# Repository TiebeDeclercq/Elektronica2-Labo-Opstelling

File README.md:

# Elektronica2-Labo-Opstelling

Complete printplaat met alle schakelingen van zowel gelijkrichting als opamps @Vives kortrijk
Met een printbare voet voor betere stabiliteit en geen kortsluiting te krijgen.
Op deze voet wordt er gewerkt met heated inserts (M3) voor het monteren van de print.

Het schema is als volgt:

Voor het solderen kan je gebruikmaken van de meegeleverde BOM file, alle componenten zijn 0805 buiten sommige TH componenten (omdat deze eigen keuze zijn en makkelijk te verangen moeten zijn)

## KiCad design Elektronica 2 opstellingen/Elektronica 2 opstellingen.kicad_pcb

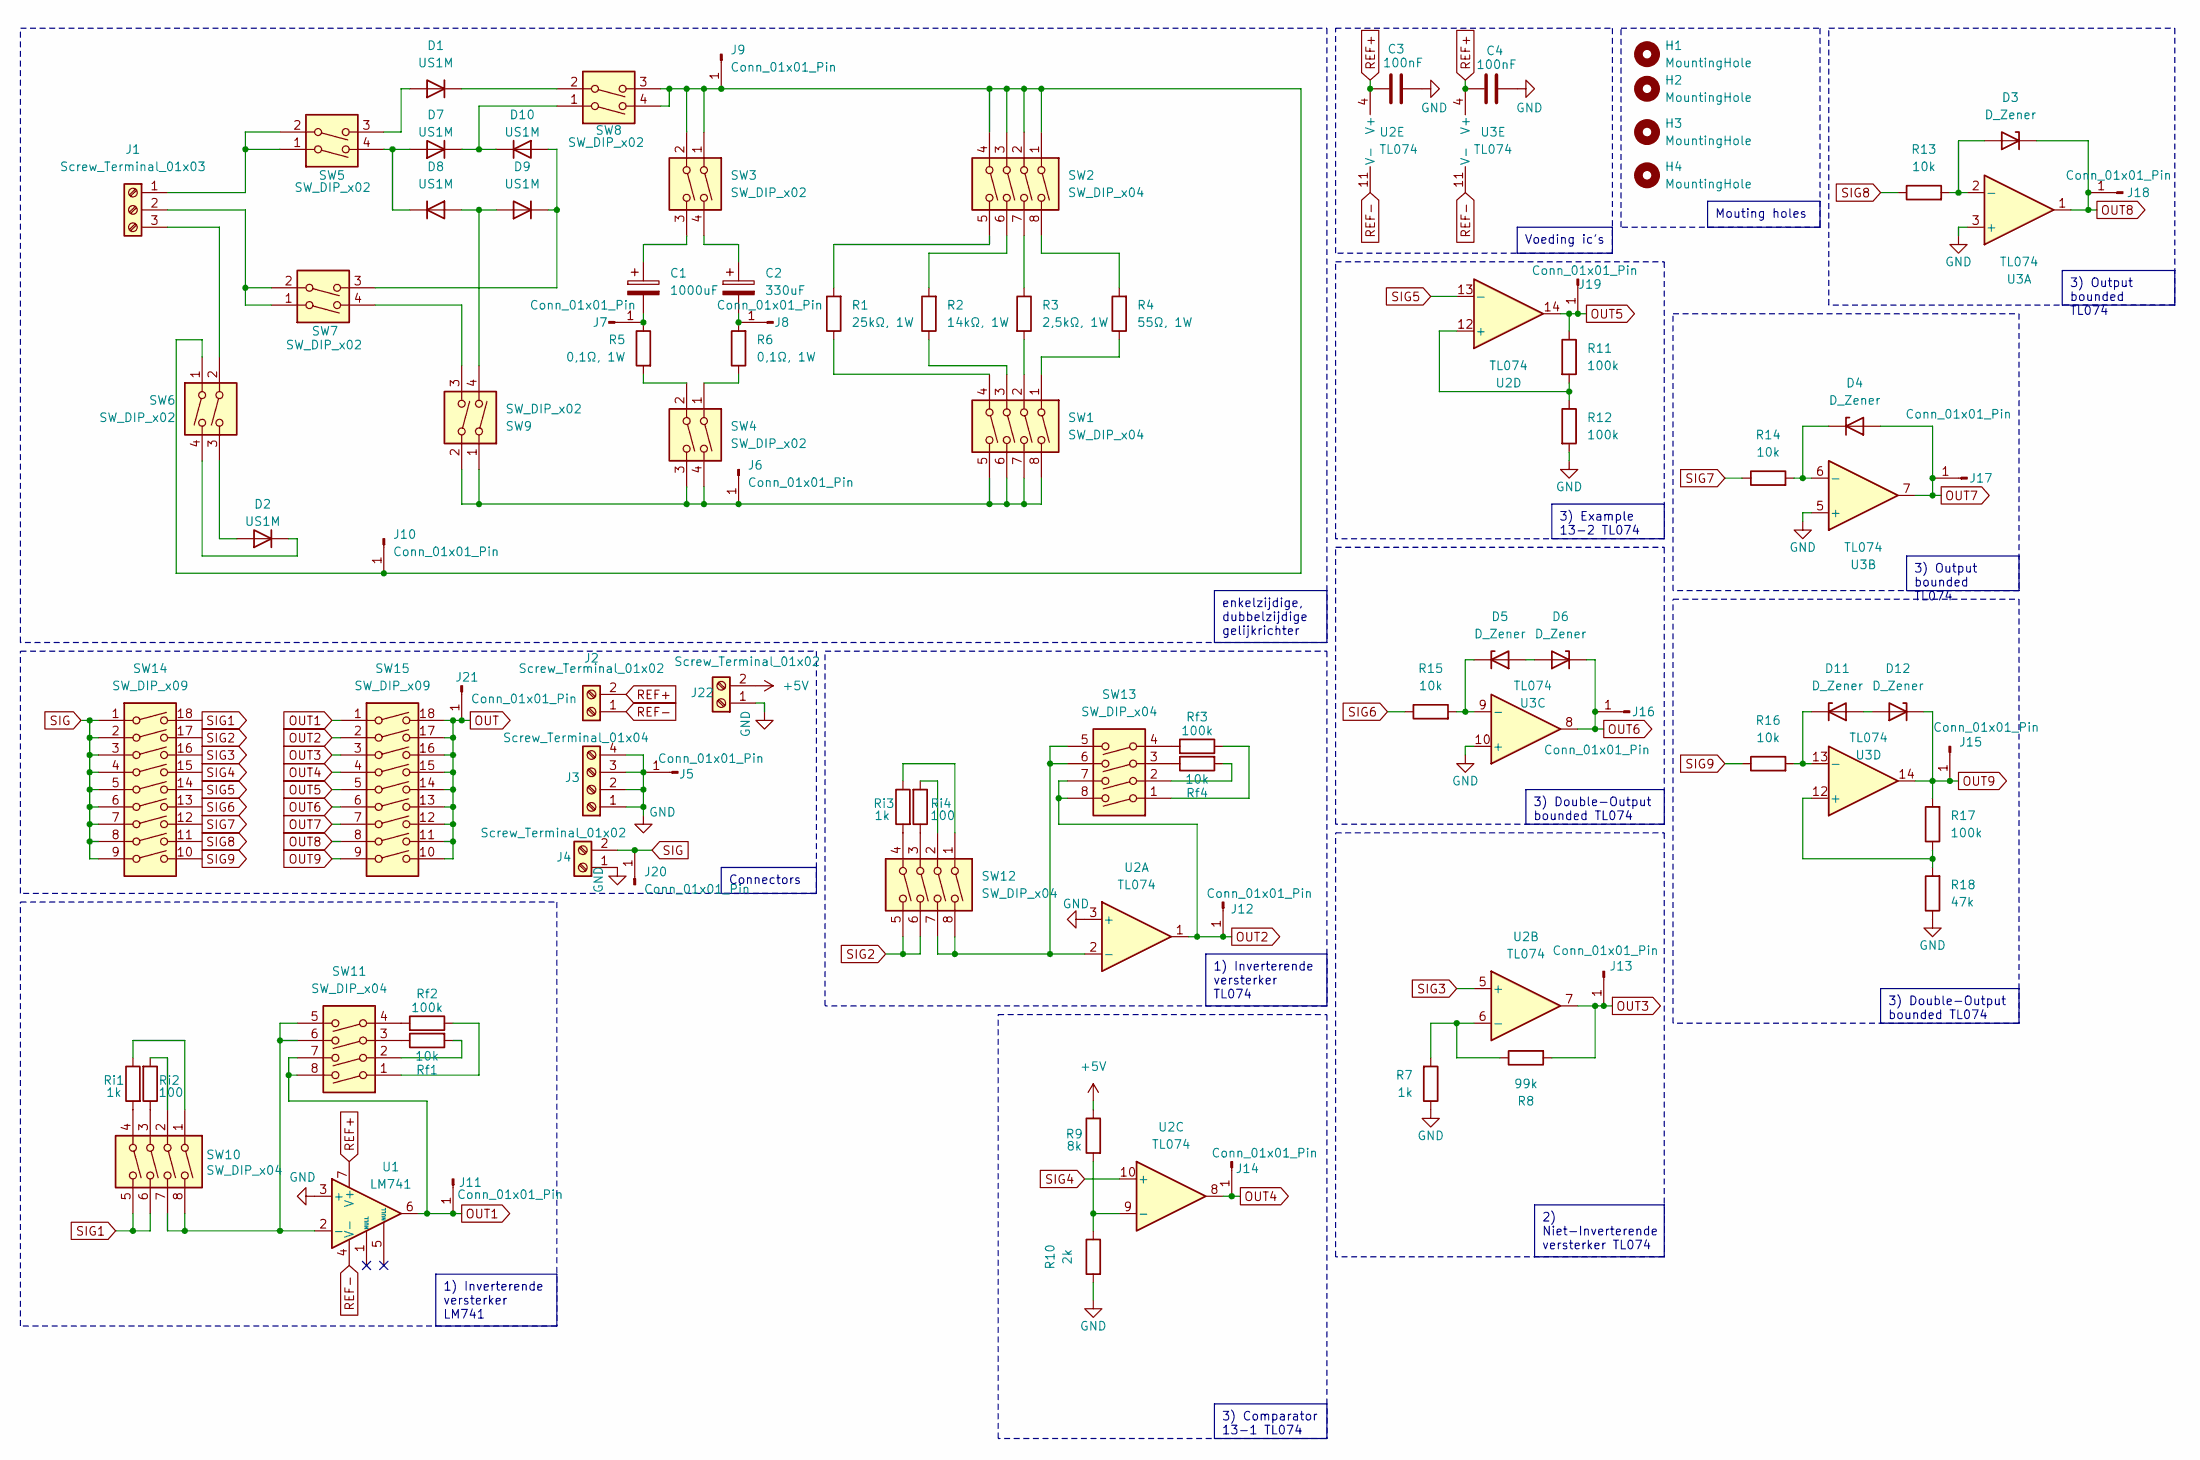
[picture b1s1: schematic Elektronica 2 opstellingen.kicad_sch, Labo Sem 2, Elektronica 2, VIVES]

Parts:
C1: 1000uF; CP_Elec_10x10.5
C2: 330uF; CP_Elec_8x10
C3, C4: 100nF; C_0805_2012Metric
D1, D2, D7, D8, D9, D10: US1M; D_SMA
D3, D4, D5, D6, D11, D12: D_Zener; D_SOD-123
H1, H2, H3, H4: MountingHole; MountingHole_3.2mm_M3
J1: Screw_Terminal_01x03; TerminalBlock_Phoenix_MKDS-1,5-3_1x03_P5.00mm_Horizontal
J2, J4, J22: Screw_Terminal_01x02; TerminalBlock_Phoenix_MKDS-1,5-2_1x02_P5.00mm_Horizontal
J3: Screw_Terminal_01x04; TerminalBlock_Phoenix_MKDS-1,5-4-5.08_1x04_P5.08mm_Horizont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
J5, J6, J7, J8, J9, J10, J11, J12, J13, J14, J15, J16, J17, J18, J19, J20, J21: Conn_01x01_Pin; PinHeader_1x01_P2.54mm_Vertical
R1: 25kΩ, 1W; R_2512_6332Metric
R2: 14kΩ, 1W; R_2512_6332Metric
R3: 2,5kΩ, 1W; R_2512_6332Metric
R4: 55Ω, 1W; R_2512_6332Metric
R5, R6: 0,1Ω, 1W; R_2512_6332Metric
R7: 1k; R_0805_2012Metric
R8: 99k; R_0805_2012Metric
R9: 8k; R_Axial_DIN0207_L6.3mm_D2.5mm_P10.16mm_Horizontal
R10: 2k; R_Axial_DIN0207_L6.3mm_D2.5mm_P10.16mm_Horizontal
R11, R12, R17: 100k; R_Axial_DIN0207_L6.3mm_D2.5mm_P10.16mm_Horizontal
R13, R14, R15, R16: 10k; R_Axial_DIN0207_L6.3mm_D2.5mm_P10.16mm_Horizontal
R18: 47k; R_Axial_DIN0207_L6.3mm_D2.5mm_P10.16mm_Horizontal
Rf1, Rf4: 10k; R_0805_2012Metric
Rf2, Rf3: 100k; R_0805_2012Metric
Ri1, Ri3: 1k; R_0805_2012Metric
Ri2, Ri4: 100; R_0805_2012Metric
SW1, SW2, SW10, SW11, SW12, SW13: SW_DIP_x04; SW_DIP_SPSTx04_Slide_9.78x12.34mm_W7.62mm_P2.54mm
SW3, SW4, SW5, SW6, SW7, SW8, SW9: SW_DIP_x02; SW_DIP_SPSTx02_Slide_9.78x7.26mm_W7.62mm_P2.54mm
SW14, SW15: SW_DIP_x09; SW_DIP_SPSTx09_Slide_9.78x25.04mm_W7.62mm_P2.54mm
U1: LM741; SOIC-8_3.9x4.9mm_P1.27mm
U2, U3: TL074; SOIC-14_3.9x8.7mm_P1.27mm

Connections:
+5V: J22.2, R9.1
GND: C3.2, C4.2, J3.1, J3.2, J3.3, J3.4, J4.1, J5.1, J22.1, R7.1, R10.2, R12.2, R18.1, U1.3 (+), U2.3 (+), U3.3 (+), U3.5 (+), U3.10 (+)
unnamed: C1.1, SW3.3
unnamed: C2.1, SW3.4
unnamed: D1.2 (A), SW5.3
unnamed: D1.1 (K), SW8.2
unnamed: D2.2 (A), SW6.3
unnamed: D2.1 (K), SW6.4
unnamed: D3.2 (A), R13.2, U3.2 (-)
unnamed: D4.1 (K), R14.2, U3.6 (-)
unnamed: D5.2 (A), D6.2 (A)
unnamed: D5.1 (K), R15.2, U3.9 (-)
unnamed: D7.2 (A), D8.1 (K), SW5.4
unnamed: D8.2 (A), D9.2 (A), SW9.4
unnamed: D9.1 (K), D10.2 (A), SW7.3
unnamed: D7.1 (K), D10.1 (K), SW8.1
unnamed: D11.2 (A), D12.2 (A)
unnamed: D11.1 (K), R16.2, U3.13 (-)
unnamed: J1.1, SW5.1, SW5.2
unnamed: J1.2, SW7.1, SW7.2
unnamed: J1.3, SW6.2
unnamed: J6.1, SW1.5, SW1.6, SW1.7, SW1.8, SW4.3, SW4.4, SW9.1, SW9.2
unnamed: C1.2, J7.1, R5.1
unnamed: C2.2, J8.1, R6.2
unnamed: J9.1, J10.1, SW2.1, SW2.2, SW2.3, SW2.4, SW3.1, SW3.2, SW6.1, SW8.3, SW8.4
unnamed: R1.1, SW1.4
unnamed: R1.2, SW2.5
unnamed: R2.1, SW1.3
unnamed: R2.2, SW2.6
unnamed: R3.1, SW2.7
unnamed: R3.2, SW1.2
unnamed: R4.1, SW1.1
unnamed: R4.2, SW2.8
unnamed: R5.2, SW4.2
unnamed: R6.1, SW4.1
unnamed: Rf1.1, SW11.3
unnamed: Rf1.2, SW11.2
unnamed: Rf2.1, SW11.1
unnamed: Rf2.2, SW11.4
unnamed: Rf3.1, SW13.1
unnamed: Rf3.2, SW13.4
unnamed: Rf4.1, SW13.3
unnamed: Rf4.2, SW13.2
unnamed: Ri1.1, SW10.1
unnamed: Ri1.2, SW10.4
unnamed: Ri2.1, SW10.3
unnamed: Ri2.2, SW10.2
unnamed: Ri3.1, SW12.1
unnamed: Ri3.2, SW12.4
unnamed: Ri4.1, SW12.3
unnamed: Ri4.2, SW12.2
unnamed: SW7.4, SW9.3
unnamed: SW10.7, SW10.8, SW11.5, SW11.6, U1.2 (-)
unnamed: SW12.7, SW12.8, SW13.5, SW13.6, U2.2 (-)
unnamed: R7.2, R8.1, U2.6 (-)
unnamed: R9.2, R10.1, U2.9 (-)
unnamed: R11.2, R12.1, U2.12 (+)
unnamed: R17.1, R18.2, U3.12 (+)
OUT: J21.1, SW15.10, SW15.11, SW15.12, SW15.13, SW15.14, SW15.15, SW15.16, SW15.17, SW15.18
OUT1: J11.1, SW11.7, SW11.8, SW15.1, U1.6
OUT2: J12.1, SW13.7, SW13.8, SW15.2, U2.1
OUT3: J13.1, R8.2, SW15.3, U2.7
OUT4: J14.1, SW15.4, U2.8
OUT5: J19.1, R11.1, SW15.5, U2.14
OUT6: D6.1 (K), J16.1, SW15.6, U3.8
OUT7: D4.2 (A), J17.1, SW15.7, U3.7
OUT8: D3.1 (K), J18.1, SW15.8, U3.1
OUT9: D12.1 (K), J15.1, R17.2, SW15.9, U3.14
REF+: C3.1, C4.1, J2.2, U1.7 (V+), U2.4 (V+), U3.4 (V+)
REF-: J2.1, U1.4 (V-), U2.11 (V-), U3.11 (V-)
SIG: J4.2, J20.1, SW14.1, SW14.2, SW14.3, SW14.4, SW14.5, SW14.6, SW14.7, SW14.8, SW14.9
SIG1: SW10.5, SW10.6, SW14.18
SIG2: SW12.5, SW12.6, SW14.17
SIG3: SW14.16, U2.5 (+)
SIG4: SW14.15, U2.10 (+)
SIG5: SW14.14, U2.13 (-)
SIG6: R15.1, SW14.13
SIG7: R14.1, SW14.12
SIG8: R13.1, SW14.11
SIG9: R16.1, SW14.10

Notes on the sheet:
3) Output bounded TL074
3) Comparator 13-1 TL074
3) Double-Output bounded TL074
Voeding ic's
Connectors
Mouting holes
1) Inverterende versterker LM741
enkelzijdige, dubbelzijdige gelijkrichter
3) Example 13-2 TL074
2) Niet-Inverterende versterker TL074
1) Inverterende versterker TL074

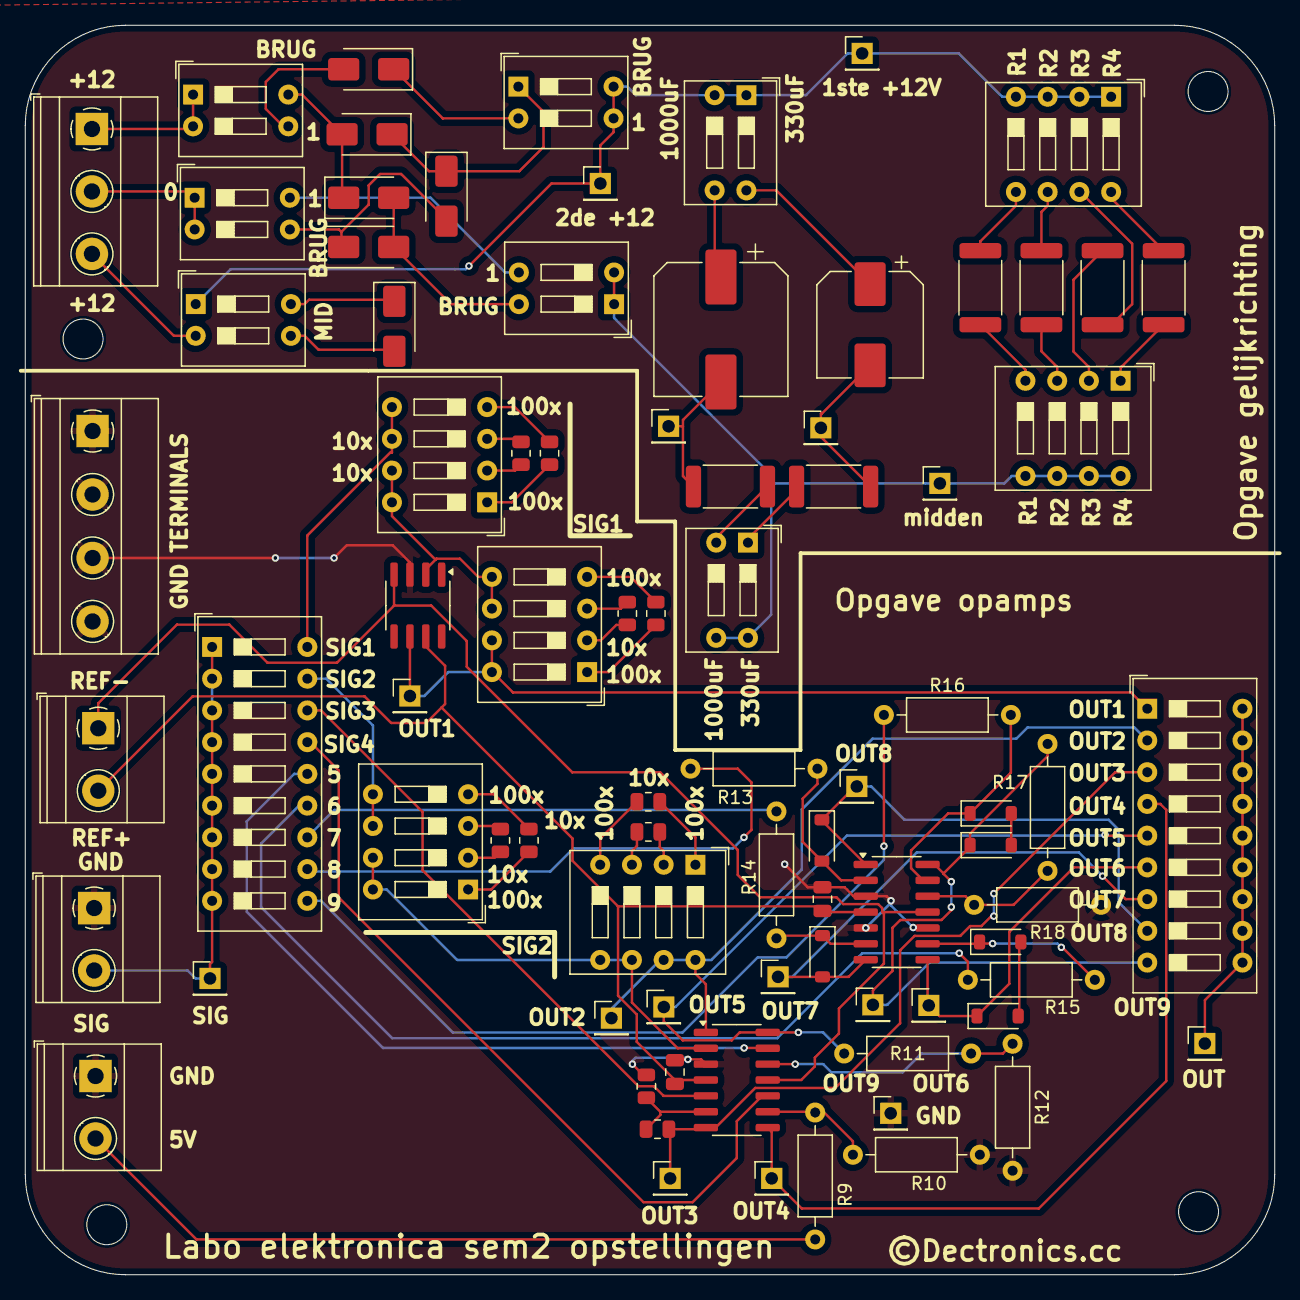
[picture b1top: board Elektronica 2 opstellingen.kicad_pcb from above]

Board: 2 copper layers, 100.0 x 100.0 mm, 86 parts (0 on the bottom side), 80 nets.

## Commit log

2025-05-21 afbeeldingen
2025-05-21 Rename sideAngle.JPG to sideAngle.jpg
2025-05-21 printfiles
2025-05-21 sssh

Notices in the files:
Elektronica 2 opstellingen/Elektronica 2 opstellingen.kicad_pcb:
©Dectronics.cc
